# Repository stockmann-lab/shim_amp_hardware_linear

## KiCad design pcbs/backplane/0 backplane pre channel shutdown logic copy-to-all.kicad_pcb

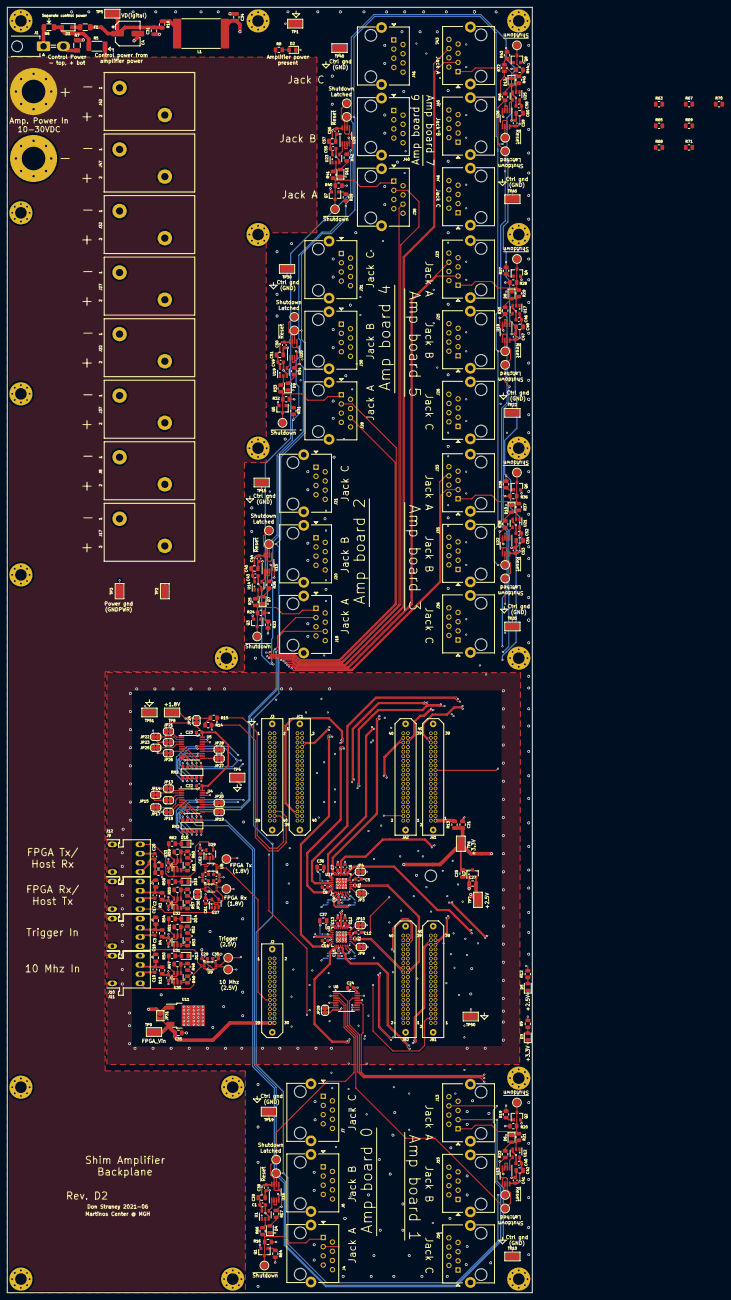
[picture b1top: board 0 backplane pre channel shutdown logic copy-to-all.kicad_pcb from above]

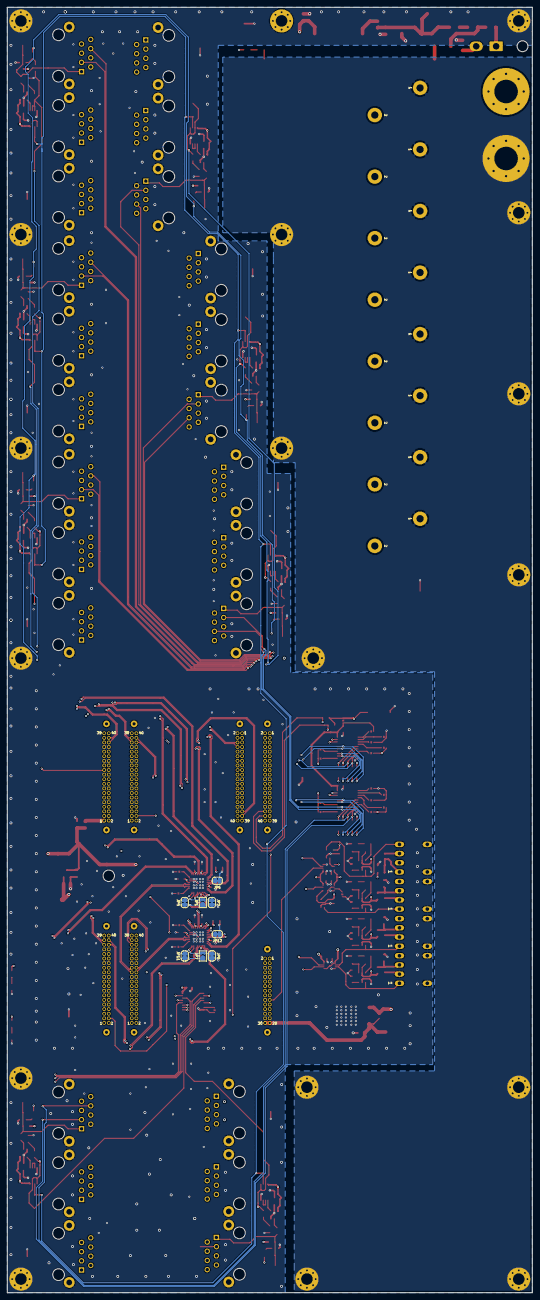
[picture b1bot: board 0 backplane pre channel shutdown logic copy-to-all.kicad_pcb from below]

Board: 6 copper layers, 145.0 x 355.0 mm, 340 parts (8 on the bottom side), 304 nets.

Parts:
C1, C2, C3, C5, C6, C7, C8, C9, C10, C11, C12, C13, C14, C15, C20, C22, C23, C24, C26, C28, C29, C30, C32, C33, C38, C40, C41, C43, C44, C46, C47, C49, C50, C52, C53, C55, C56, C58, C59, C61, C62, C63, C64, C65, C66: 100nF 50V X7R; C_0603_1608Metric
C4: 100uF 35V alum.; CP_Elec_6.3x9.9
C16, C17, C18, C19, C21, C25, C27, C31, C34, C35, C36, C37, C39, C42, C45, C48, C51, C54, C57, C60: 1uF 50V X7R; C_0805_2012Metric
D1: PMEG6010; D_SOD-123F
D2, D3, D5: Green; LED_0805_2012Metric
D4, D6, D7, D8, D9, D10, D11, D12: Red; LED_0805_2012Metric
D13, D14, D15, D16: Yellow; LED_0805_2012Metric
F1: TBD; Fuse_1206_3216Metric
H1, H2: 1/4", M6; MountingHole_6.5mm_Pad_Via
H3, H4, H5, H6, H7, H8, H9, H10, H11, H12, H13, H14, H15, H16, H17, H18, H19, H20: #4/M3; MountingHole_3.2mm_M3_Pad_Via
J1: Conn_01x02; Molex_Mini-Fit_Jr_5569-02A2_2x01_P4.20mm_Horizontal
J2: Conn_02x15_Odd_Even; Conn_Samtec_TFM-115-x1,3-x-D-WT
J3: Conn_02x20_Odd_Even; Conn_Samtec_TFM-120-x1,3-x-D-WT
J4, J6, J7, J13, J15, J16, J18, J20, J21, J23, J25, J26, J28, J30, J31, J33, J35, J36, J38, J40, J41, J43, J45, J46: RJ45_Shielded; RJ45_Amphenol_RJE06-188-1x20
J8, J17, J22, J27, J32, J37, J42, J47: Conn_01x02; Connector_Phoenix_1792229
J9, J10, J11: AFBR-2624Z; AFBR-xx2xZ
J12: AFBR-1624Z; AFBR-xx2xZ
JA1, JA2: Conn_02x20_Odd_Even; Conn_Samtec_TFM-120-x1,3-x-D-WT
JB1, JB2: Conn_02x20_Odd_Even; Conn_Samtec_TFM-120-x1,3-x-D-WT
JC1: Conn_02x20_Odd_Even; Conn_Samtec_TFM-120-x1,3-x-D-WT
JP1, JP7: Jumper_NC_Small; SolderJumper-2_P1.3mm_Open_TrianglePad1.0x1.5mm
JP2, JP3, JP4, JP5, JP6, JP8, JP9, JP10, JP11, JP12, JP13, JP14, JP15, JP17, JP18, JP19, JP20, JP21, JP22, JP23, JP24, JP25, JP26, JP27, JP28, JP29, JP30: Jumper_NC_Small; SolderJumper-2_P1.3mm_Bridged_RoundedPad1.0x1.5mm
JP31: Jumper_NO_Small; SolderJumper-2_P1.3mm_Open_TrianglePad1.0x1.5mm
L1: 500nH; L_Coilcraft_2929SQ-501
Q1, Q2, Q3, Q4, Q5, Q6, Q7, Q8: MMBT3904; SOT-23
R1, R2: 100; R_0402_1005Metric
R3, R4, R10, R11, R13, R18: 1; R_0805_2012Metric
R5: 10 0.25W; R_2010_5025Metric
R6, R7: 1; R_1206_3216Metric
R8: 15K; R_0805_2012Metric
R9, R16, R20, R21, R24, R25, R28, R29, R32, R33, R36, R37, R40, R41, R44, R45, R50, R54, R58, R62, R66: 1K; R_0805_2012Metric
R12: 560; R_0805_2012Metric
R14, R15: 4.7K; R_0805_2012Metric
R17, R22, R26, R30, R34, R38, R42, R46: 3.3K; R_0805_2012Metric
R19, R23, R27, R31, R35, R39, R43, R63, R64, R65, R67, R68, R69, R70, R71, R72: 20K; R_0805_2012Metric
R47, R51, R55, R59: 10K; R_0805_2012Metric
R48, R52, R56, R60: 6.81K; R_0805_2012Metric
R49, R53, R57, R61: 180K; R_0805_2012Metric
RN1, RN2: 4.7K; CTS_745C
TP1, TP2, TP3, TP4, TP5, TP6, TP7, TP8, TP9, TP10, TP15, TP19, TP22, TP30, TP35, TP40, TP45, TP50, TP51: TestPoint_Flag; TestPoint_Keystone_5019_Minature
TP11, TP14, TP16, TP20, TP21, TP23, TP26, TP29, TP31, TP34, TP36, TP39, TP41, TP44, TP46, TP49, TP52, TP53, TP54, TP55, TP56, TP57, TP58, TP59, TP60, TP61, TP62, TP63: TestPoint; TestPoint_Pad_D2.0mm
U1, U12, U14, U17, U19, U21, U23, U25, U27, U29: 74LVC1G14; SOT-23-5
U2, U3: CDCUN1208LP; VQFN-32-1EP_5x5mm_P0.5mm_EP3.45x3.45mm
U4, U5: PCA9544APW; TSSOP-20_4.4x6.5mm_P0.65mm
U6: 74HC151; TSSOP-16_4.4x5mm_P0.65mm
U7: AP2120N-2.5; SOT-23
U8, U9, U10: 74LVC2T45; VSSOP-8_2.3x2mm_P0.5mm
U11: 78M15; TO-252-2
U13, U15, U16, U18, U20, U22, U24, U26: 74LVC2G02; VSSOP-8_3.0x3.0mm_P0.65mm
U28: Snickerdoodle
U30, U31, U32, U33: LTC6993xS6-2; TSOT-23-6

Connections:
+1.8V: C26.2, C33.2, J3.3, JP24.1, R14.1, R15.1, TP8.1, U8.1, U8.5, U10.8
+2.5V: C1.1, C24.1, C27.2, C30.2, C38.1, C39.2, C40.1, C41.1, C42.2, C43.1, C44.1, C45.2, C46.1, C47.1, C48.2, C49.1, C50.1, C51.2, C52.1, C53.1, C54.2, C55.1, C56.1, C57.2, C58.1, C59.1, C60.2, JA1.3, JA2.3, JB1.3, JB2.3, JC1.3, R12.1, TP7.1, U1.5, U6.16, U7.2, U9.8, U12.5, U13.8, U14.5, U15.8, U16.8, U17.5, U18.8, U19.5, U20.8, U21.5, U22.8, U23.5, U24.8, U25.5, U26.8
+3V3: C5.1, C6.1, C7.1, C8.1, C9.1, C11.1, C12.1, C13.1, C14.1, C15.1, C21.2, C25.2, C28.2, C29.2, C32.2, C36.2, C37.2, C61.2, C62.2, C63.2, C64.2, C65.2, C66.2, JP1.1, JP5.1, JP7.1, JP11.1, JP17.2, JP18.2, JP19.2, JP20.2, JP25.2, JP26.2, JP27.2, JP28.2, R3.1, R4.1, R9.1, R10.1, R11.1, R13.2, R16.1, R20.1, R24.1, R28.1, R32.1, R36.1, R40.1, R44.1, R47.1, R51.1, R55.1, R59.1, RN1.5, RN1.10, RN2.5, RN2.10, TP6.1, U2.5, U2.11, U2.14, U2.22, U2.27, U3.5, U3.11, U3.14, U3.22, U3.27, U7.3, U8.8, U9.1, U9.5, U10.1, U10.5, U27.5, U29.5, U30.5, U31.5, U32.5, U33.5
+VDC: H1.1, J8.2, J17.2, J22.2, J27.2, J32.2, J37.2, J42.2, J47.2, R5.2, R8.1, TP2.1
/ADC_MISO+0: J6.8, JB2.11
/ADC_MISO+1: J15.8, JB1.14
/ADC_MISO+2: J20.8, JC1.14
/ADC_MISO+3: J35.8, JB1.26
/ADC_MISO+4: J30.8, JC1.32
/ADC_MISO+5: J25.8, JA1.14
/ADC_MISO+6: J40.8, JA2.29
/ADC_MISO+7: J45.8, JA1.35
/ADC_MISO-0: J6.7, JB2.13
/ADC_MISO-1: J15.7, JB1.12
/ADC_MISO-2: J20.7, JC1.12
/ADC_MISO-3: J35.7, JB1.24
/ADC_MISO-4: J30.7, JC1.30
/ADC_MISO-5: J25.7, JA1.12
/ADC_MISO-6: J40.7, JA2.31
/ADC_MISO-7: J45.7, JA1.37
/ADC_MOSI+0: J4.4, JB2.8
/ADC_MOSI+1: J13.4, JB1.17
/ADC_MOSI+2: J18.4, JC1.23
/ADC_MOSI+3: J33.4, JB2.29
/ADC_MOSI+4: J28.4, JC1.5
/ADC_MOSI+5: J23.4, JA1.17
/ADC_MOSI+6: J38.4, JA2.14
/ADC_MOSI+7: J43.4, JA2.32
/ADC_MOSI-0: J4.5, JB2.6
/ADC_MOSI-1: J13.5, JB1.19
/ADC_MOSI-2: J18.5, JC1.25
/ADC_MOSI-3: J33.5, JB2.31
/ADC_MOSI-4: J28.5, JC1.7
/ADC_MOSI-5: J23.5, JA1.19
/ADC_MOSI-6: J38.5, JA2.12
/ADC_MOSI-7: J43.5, JA2.30
/Activitiy Indicator (Rx)/In: J9.1, U27.2, U32.1
/Activity Indicator (Trigger)/In: J10.1, U9.2, U31.1
/Activity Indicator (Tx)/In: J12.4, U29.4, U33.1
/Amp board 0 interface/~Shutdown: J4.1, Q1.3, R16.2, R66.2, TP54.1
/Amp board 1 interface/~Shutdown: J13.1, Q2.3, R20.2, R21.2, TP55.1
/Amp board 2 interface/~Shutdown: J18.1, Q3.3, R24.2, R25.2, TP56.1
/Amp board 3 interface/~Shutdown: J33.1, Q6.3, R36.2, R37.2, TP59.1
/Amp board 4 interface/~Shutdown: J28.1, Q5.3, R32.2, R33.2, TP58.1
/Amp board 5 interface/~Shutdown: J23.1, Q4.3, R28.2, R29.2, TP57.1
/Amp board 6 interface/~Shutdown: J38.1, Q7.3, R40.2, R41.2, TP60.1
/Amp board 7 interface/~Shutdown: J43.1, Q8.3, R44.2, R45.2, TP61.1
/DAC_MISO+0: J6.2, JB2.14
/DAC_MISO+1: J15.2, JB1.11
/DAC_MISO+2: J20.2, JC1.17
/DAC_MISO+3: J35.2, JB1.29
/DAC_MISO+4: J30.2, JC1.38
/DAC_MISO+5: J25.2, JA1.11
/DAC_MISO+6: J40.2, JA2.20
/DAC_MISO+7: J45.2, JA1.26
/DAC_MISO-0: J6.1, JB2.12
/DAC_MISO-1: J15.1, JB1.13
/DAC_MISO-2: J20.1, JC1.19
/DAC_MISO-3: J35.1, JB1.31
/DAC_MISO-4: J30.1, JC1.36
/DAC_MISO-5: J25.1, JA1.13
/DAC_MISO-6: J40.1, JA2.18
/DAC_MISO-7: J45.1, JA1.24
/DAC_MOSI+0: J7.5, JB2.20
/DAC_MOSI+1: J16.5, JB1.5
/DAC_MOSI+2: J21.5, JC1.11
/DAC_MOSI+3: J36.5, JB1.23
/DAC_MOSI+4: J31.5, JA2.8
/DAC_MOSI+5: J26.5, JA1.5
/DAC_MOSI+6: J41.5, JA2.26
/DAC_MOSI+7: J46.5, JA1.32
/DAC_MOSI-0: J7.4, JB2.18
/DAC_MOSI-1: J16.4, JB1.7
/DAC_MOSI-2: J21.4, JC1.13
/DAC_MOSI-3: J36.4, JB1.25
/DAC_MOSI-4: J31.4, JA2.6
/DAC_MOSI-5: J26.4, JA1.7
/DAC_MOSI-6: J41.4, JA2.24
/DAC_MOSI-7: J46.4, JA1.30
/FPGA Board, Signal Distribution/10Mhz: J11.1, U9.3, U30.1
/FPGA Board, Signal Distribution/10Mhz_2.5: JB2.38, TP62.1, U9.6
/FPGA Board, Signal Distribution/FPGA_Vin: C35.2, J2.29, J2.30, JP31.2, TP9.1, U11.3
/FPGA Board, Signal Distribution/I2C_Pwr: C22.1, C23.1, JP21.1, JP24.2, U4.20, U5.20
/FPGA Board, Signal Distribution/LDAC+: JB2.26, R2.1, U3.4
/FPGA Board, Signal Distribution/LDAC-: JB2.24, R2.2, U3.3
/FPGA Board, Signal Distribution/SCL: J3.38, R15.2, U4.18, U5.18
/FPGA Board, Signal Distribution/SDA: J3.36, R14.2, U4.19, U5.19
/FPGA Board, Signal Distribution/Shutdown_Sense: JA2.4, U6.5
/FPGA Board, Signal Distribution/Shutdown_Sense_Sel0: JB2.4, U6.11
/FPGA Board, Signal Distribution/Shutdown_Sense_Sel1: JB1.4, U6.10
/FPGA Board, Signal Distribution/Shutdown_Sense_Sel2: JC1.4, U6.9
/FPGA Board, Signal Distribution/Trigger_2.5: JB2.36, TP53.1, U9.7
/FPGA Board, Signal Distribution/UART_Rx_FPGA: U10.2, U27.4
/FPGA Board, Signal Distribution/UART_Rx_FPGA_1.8: J3.37, TP63.1, U10.7
/FPGA Board, Signal Distribution/UART_Tx_FPGA: U8.6, U29.2
/FPGA Board, Signal Distribution/UART_Tx_FPGA_1.8: J3.35, TP52.1, U8.3
/FPGA Board, Signal Distribution/~FPGA_Rst_1.8: J2.19, U8.2
/FPGA Board, Signal Distribution/~SCKI+: JB2.23, R1.1, U2.4
/FPGA Board, Signal Distribution/~SCKI-: JB2.25, R1.2, U2.3
/SCKI+0: J7.2, U2.26
/SCKI+1: J16.2, U2.29
/SCKI+2: J21.2, U2.24
/SCKI+3: J36.2, U2.10
/SCKI+4: J31.2, U2.16
/SCKI+5: J26.2, U2.21
/SCKI+6: J41.2, U2.18
/SCKI+7: J46.2, U2.13
/SCKI-0: J7.1, U2.25
/SCKI-1: J16.1, U2.28
/SCKI-2: J21.1, U2.23
/SCKI-3: J36.1, U2.9
/SCKI-4: J31.1, U2.15
/SCKI-5: J26.1, U2.20
/SCKI-6: J41.1, U2.17
/SCKI-7: J46.1, U2.12
/SCKO+0: J6.5, JB2.35
/SCKO+1: J15.5, JB1.38
/SCKO+2: J20.5, JC1.8
/SCKO+3: J35.5, JB1.35
/SCKO+4: J30.5, JC1.35
/SCKO+5: J25.5, JA1.38
/SCKO+6: J40.5, JA2.38
/SCKO+7: J45.5, JA2.35
/SCKO-0: J6.4, JB2.37
/SCKO-1: J15.4, JB1.36
/SCKO-2: J20.4, JC1.6
/SCKO-3: J35.4, JB1.37
/SCKO-4: J30.4, JC1.37
/SCKO-5: J25.4, JA1.36
/SCKO-6: J40.4, JA2.36
/SCKO-7: J45.4, JA2.37
/SCL0: J4.3, RN1.2, U4.6
/SCL1: J13.3, RN1.4, U4.9
/SCL2: J18.3, RN1.8, U4.13
/SCL3: J33.3, RN1.6, U4.16
/SCL4: J28.3, RN2.2, U5.6
/SCL5: J23.3, RN2.4, U5.9
/SCL6: J38.3, RN2.8, U5.13
/SCL7: J43.3, RN2.6, U5.16
/SDA0: J4.6, RN1.1, U4.5
/SDA1: J13.6, RN1.3, U4.8
/SDA2: J18.6, RN1.9, U4.12
/SDA3: J33.6, RN1.7, U4.15
/SDA4: J28.6, RN2.1, U5.5
/SDA5: J23.6, RN2.3, U5.8
/SDA6: J38.6, RN2.9, U5.12
/SDA7: J43.6, RN2.7, U5.15
/Shutdown_Force: JA1.23, R19.2, R23.2, R27.2, R31.2, R35.2, R39.2, R43.2, R64.2
/Shutdown_Sense0: R17.2, R63.2, TP26.1, U6.4, U16.2, U16.3
/Shutdown_Sense1: R22.2, R65.2, TP14.1, U6.3, U13.2, U13.3
/Shutdown_Sense2: R26.2, R67.2, TP20.1, U6.2, U15.2, U15.3
/Shutdown_Sense3: R38.2, R70.2, TP39.1, U6.1, U22.2, U22.3
/Shutdown_Sense4: R34.2, R69.2, TP34.1, U6.15, U20.2, U20.3
/Shutdown_Sense5: R30.2, R68.2, TP29.1, U6.14, U18.2, U18.3
/Shutdown_Sense6: R42.2, R71.2, TP44.1, U6.13, U24.2, U24.3
/Shutdown_Sense7: R46.2, R72.2, TP49.1, U6.12, U26.2, U26.3
/~ADC_CS+0: J4.7, JB2.17
/~ADC_CS+1: J13.7, JB1.8
/~ADC_CS+2: J18.7, JC1.29
/~ADC_CS+3: J33.7, JB2.32
/~ADC_CS+4: J28.7, JC1.26
/~ADC_CS+5: J23.7, JA1.8
/~ADC_CS+6: J38.7, JA2.5
/~ADC_CS+7: J43.7, JA2.17
/~ADC_CS-0: J4.8, JB2.19
/~ADC_CS-1: J13.8, JB1.6
/~ADC_CS-2: J18.8, JC1.31
/~ADC_CS-3: J33.8, JB2.30
/~ADC_CS-4: J28.8, JC1.24
/~ADC_CS-5: J23.8, JA1.6
/~ADC_CS-6: J38.8, JA2.7
/~ADC_CS-7: J43.8, JA2.19
/~DAC_CS+0: J7.6, JB2.5
/~DAC_CS+1: J16.6, JB1.20
/~DAC_CS+2: J21.6, JC1.20
/~DAC_CS+3: J36.6, JB1.32
/~DAC_CS+4: J31.6, JA2.11
/~DAC_CS+5: J26.6, JA1.20
/~DAC_CS+6: J41.6, JA2.23
/~DAC_CS+7: J46.6, JA1.29
/~DAC_CS-0: J7.3, JB2.7
/~DAC_CS-1: J16.3, JB1.18
/~DAC_CS-2: J21.3, JC1.18
/~DAC_CS-3: J36.3, JB1.30
/~DAC_CS-4: J31.3, JA2.13
/~DAC_CS-5: J26.3, JA1.18
/~DAC_CS-6: J41.3, JA2.25
/~DAC_CS-7: J46.3, JA1.31
/~LDAC+0: J7.8, U3.25
/~LDAC+1: J16.8, U3.28
/~LDAC+2: J21.8, U3.23
/~LDAC+3: J36.8, U3.9
/~LDAC+4: J31.8, U3.12
/~LDAC+5: J26.8, U3.17
/~LDAC+6: J41.8, U3.15
/~LDAC+7: J46.8, U3.20
/~LDAC-0: J7.7, U3.26
/~LDAC-1: J16.7, U3.29
/~LDAC-2: J21.7, U3.24
/~LDAC-3: J36.7, U3.10
/~LDAC-4: J31.7, U3.13
/~LDAC-5: J26.7, U3.18
/~LDAC-6: J41.7, U3.16
/~LDAC-7: J46.7, U3.21
/~Shutdown_Reset: TP11.1, TP16.1, TP21.1, TP23.1, TP31.1, TP36.1, TP41.1, TP46.1, U13.6, U15.6, U16.6, U18.6, U20.6, U22.6, U24.6, U26.6
GND: C1.2, C2.2, C3.2, C4.2, C5.2, C6.2, C7.2, C8.2, C9.2, C10.2, C11.2, C12.2, C13.2, C14.2, C15.2, C16.1, C17.1, C18.1, C19.1, C20.2, C21.1, C22.2, C23.2, C24.2, C25.1, C26.1, C27.1, C28.1, C29.1, C30.1, C31.1, C32.1, C33.1, C34.1, C35.1, C36.1, C37.1, C38.2, C39.1, C40.2, C41.2, C42.1, C43.2, C44.2, C45.1, C46.2, C47.2, C48.1, C49.2, C50.2, C51.1, C52.2, C53.2, C54.1, C55.2, C56.2, C57.1, C58.2, C59.2, C60.1, C61.1, C62.1, C63.1, C64.1, C65.1, C66.1, D3.1, D4.1, D5.1, D6.1, D7.1, D8.1, D9.1, D10.1, D11.1, D12.1, D13.1, D14.1, D15.1, D16.1, H3.1, H4.1, H6.1, H8.1, H10.1, H12.1, H13.1, H15.1, J2.5, J2.6, J2.9, J2.10, J2.20, J2.26, J2.27, J2.28, J3.9, J3.10, J3.15, J3.16, J3.21, J3.22, J3.27, J3.28, J3.33, J3.34, J4.2, J4.SH, J6.SH, J7.SH, J9.2, J9.5, J9.8, J10.2, J10.5, J10.8, J11.2, J11.5, J11.8, J12.3, J12.5, J12.8, J13.2, J13.SH, J15.SH, J16.SH, J18.2, J18.SH, J20.SH, J21.SH, J23.2, J23.SH, J25.SH, J26.SH, J28.2, J28.SH, J30.SH, J31.SH, J33.2, J33.SH, J35.SH, J36.SH, J38.2, J38.SH, J40.SH, J41.SH, J43.2, J43.SH, J45.SH, J46.SH, JA1.9, JA1.10, JA1.15, JA1.16, JA1.21, JA1.22, JA1.27, JA1.28, JA1.33, JA1.34, JA2.9, JA2.10, JA2.15, JA2.16, JA2.21, JA2.22, JA2.27, JA2.28, JA2.33, JA2.34, JB1.9, JB1.10, JB1.15, JB1.16, JB1.21, JB1.22, JB1.27, JB1.28, JB1.33, JB1.34, JB2.9, JB2.10, JB2.15, JB2.16, JB2.21, JB2.22, JB2.27, JB2.28, JB2.33, JB2.34, JC1.9, JC1.10, JC1.15, JC1.16, JC1.21, JC1.22, JC1.27, JC1.28, JC1.33, JC1.34, JP2.2, JP3.1, JP4.1, JP6.1, JP8.2, JP9.1, JP10.1, JP12.1, JP13.1, JP14.1, JP15.1, JP22.1, JP23.1, JP29.1, JP30.1, Q1.2, Q2.2, Q3.2, Q4.2, Q5.2, Q6.2, Q7.2, Q8.2, R7.1, R48.2, R49.2, R52.2, R53.2, R56.2, R57.2, R60.2, R61.2, TP1.1, TP4.1, TP10.1, TP15.1, TP19.1, TP22.1, TP30.1, TP35.1, TP40.1, TP45.1, TP50.1, TP51.1, U1.3, U2.6, U2.7, U2.33, U3.6, U3.7, U3.33, U4.10, U5.10, U6.8, U7.1, U8.4, U9.4, U10.4, U11.2, U12.3, U13.4, U14.3, U15.4, U16.4, U17.3, U18.4, U19.3, U20.4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
GNDPWR: D2.1, H2.1, H5.1, H7.1, H9.1, H11.1, H14.1, H16.1, H17.1, H18.1, H19.1, H20.1, J8.1, J17.1, J22.1, J27.1, J32.1, J37.1, J42.1, J47.1, TP3.1
unnamed: C10.1, C18.2, J11.3, R10.2
unnamed: C2.1, C16.2, J9.3, R3.2
unnamed: C3.1, C17.2, J10.3, R4.2
unnamed: C19.2, C20.1, J12.1, R11.2
unnamed: C34.2, JP31.1, L1.2, U11.1
unnamed: D1.1, F1.2
unnamed: D1.2, R5.1, R6.1
unnamed: D2.2, R8.2
unnamed: D3.2, R9.2
unnamed: D4.2, R17.1
unnamed: D5.2, R12.2
unnamed: D6.2, R22.1
unnamed: D7.2, R26.1
unnamed: D8.2, R30.1
unnamed: D9.2, R34.1
unnamed: D10.2, R38.1
unnamed: D11.2, R42.1
unnamed: D12.2, R46.1
unnamed: D13.2, R50.2
unnamed: D14.2, R54.2
unnamed: D15.2, R58.2
unnamed: D16.2, R62.2
unnamed: J1.1, R6.2
unnamed: J1.2, R7.2
unnamed: JA1.1, R13.1
unnamed: JP1.2, JP2.1, U2.31
unnamed: JP3.2, U2.2
unnamed: JP4.2, U2.8
unnamed: JP5.2, U2.32
unnamed: JP6.2, U2.19
unnamed: JP7.2, JP8.1, U3.31
unnamed: JP9.2, U3.2
unnamed: JP10.2, U3.8
unnamed: JP11.2, U3.32
unnamed: JP12.2, U3.19
unnamed: JP13.2, U4.1
unnamed: JP14.2, U4.2
unnamed: JP15.2, U4.3
unnamed: JP17.1, U4.4
unnamed: JP18.1, U4.7
unnamed: JP19.1, U4.11
unnamed: JP20.1, U4.14
unnamed: JP21.2, U5.1
unnamed: JP22.2, U5.2
unnamed: JP23.2, U5.3
unnamed: JP25.1, U5.4
unnamed: JP26.1, U5.7
unnamed: JP27.1, U5.11
unnamed: JP28.1, U5.14
unnamed: JP29.2, U6.7
unnamed: JP30.2, U10.3
unnamed: L1.1, R18.1
unnamed: Q1.1, R63.1, R64.1
unnamed: Q2.1, R19.1, R65.1
unnamed: Q3.1, R23.1, R67.1
unnamed: Q4.1, R27.1, R68.1
unnamed: Q5.1, R31.1, R69.1
unnamed: Q6.1, R35.1, R70.1
unnamed: Q7.1, R39.1, R71.1
unnamed: Q8.1, R43.1, R72.1
unnamed: R21.1, U12.2
unnamed: R25.1, U14.2
unnamed: R29.1, U17.2
unnamed: R33.1, U19.2
unnamed: R37.1, U21.2
unnamed: R41.1, U23.2
unnamed: R45.1, U25.2
unnamed: R47.2, R48.1, U30.4
unnamed: R49.1, U30.3
unnamed: R50.1, U30.6
unnamed: R51.2, R52.1, U31.4
unnamed: R53.1, U31.3
unnamed: R54.1, U31.6
unnamed: R55.2, R56.1, U32.4
unnamed: R57.1, U32.3
unnamed: R58.1, U32.6
unnamed: R59.2, R60.1, U33.4
unnamed: R61.1, U33.3
unnamed: R62.1, U33.6
unnamed: R66.1, U1.2
unnamed: U1.4, U16.1
unnamed: U12.4, U13.1
unnamed: U13.5, U13.7
unnamed: U14.4, U15.1
unnamed: U15.5, U15.7
unnamed: U16.5, U16.7
unnamed: U17.4, U18.1
unnamed: U18.5, U18.7
unnamed: U19.4, U20.1
unnamed: U20.5, U20.7
unnamed: U21.4, U22.1
unnamed: U22.5, U22.7
unnamed: U23.4, U24.1
unnamed: U24.5, U24.7
unnamed: U25.4, U26.1
unnamed: U26.5, U26.7
VD: C4.1, C31.2, F1.1, R18.2, TP5.1

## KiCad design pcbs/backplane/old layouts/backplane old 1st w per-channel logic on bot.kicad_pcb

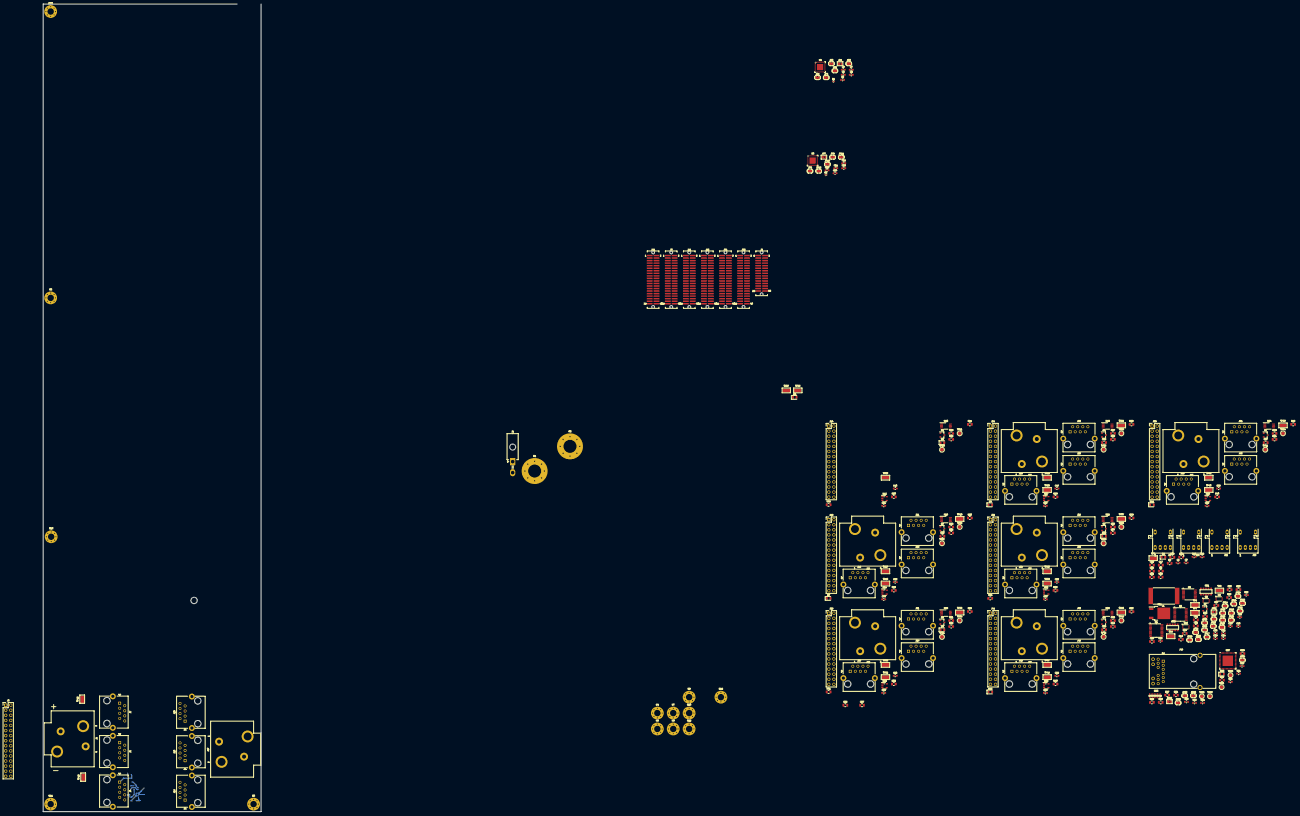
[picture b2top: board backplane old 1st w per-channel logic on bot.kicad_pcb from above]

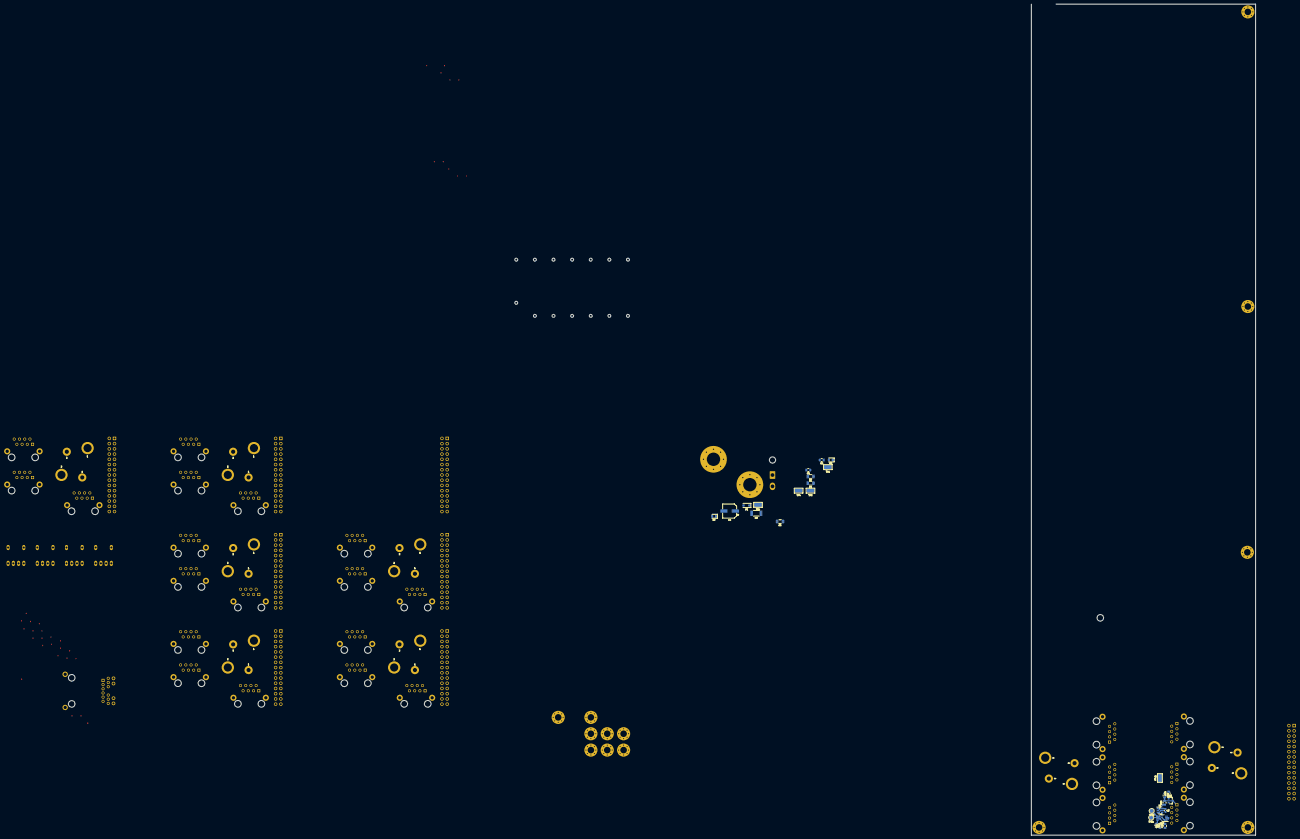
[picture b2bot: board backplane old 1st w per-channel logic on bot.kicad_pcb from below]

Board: 2 copper layers, 109.0 x 404.0 mm, 331 parts (27 on the bottom side), 338 nets.

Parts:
C1, C2, C3, C5, C6, C7, C8, C9, C10, C11, C12, C13, C14, C15, C20, C22, C23, C24, C26, C28, C29, C30, C32, C33, C38, C40, C41, C43, C44, C46, C47, C49, C50, C52, C53, C55, C56, C58, C59, C62, C63, C64, C65: 100nF 50V X7R; C_0603_1608Metric
C4: 100uF 35V alum.; CP_Elec_6.3x9.9
C16, C17, C18, C19, C21, C25, C27, C31, C34, C35, C36, C37, C39, C42, C45, C48, C51, C54, C57, C60: 1uF 50V X7R; C_0805_2012Metric
C61: 10nF 50V X7R; C_0603_1608Metric
C66: 100pF 50V NP0; C_0603_1608Metric
D1: PMEG6010; D_SOD-123F
D2, D3, D5: Green; LED_0805_2012Metric
D4, D6, D7, D8, D9, D10, D11, D12, D13: Red; LED_0805_2012Metric
F1: TBD; Fuse_1206_3216Metric
H1, H2: 1/4", M6; MountingHole_6.5mm_Pad_Via
H3, H4, H5, H6, H7, H8, H9, H10, H11, H12, H13, H14, H15: #4/M3; MountingHole_3.2mm_M3_Pad_Via
J1: Conn_01x02; Molex_Mini-Fit_Jr_5569-02A2_2x01_P4.20mm_Horizontal
J2: Conn_02x15_Odd_Even; Conn_Samtec_TFM-115-x2-L-D-A
J3: Conn_02x20_Odd_Even; Conn_Samtec_TFM-120-x2-L-D-A
J4, J6, J7, J13, J15, J16, J18, J20, J21, J23, J25, J26, J28, J30, J31, J33, J35, J36, J38, J40, J41, J43, J45, J46: RJ45_Shielded; RJ45_Amphenol_RJE06-188-1x20
J5, J14, J19, J24, J29, J34, J39, J44: Conn_02x15; PinHeader_2x15_P2.54mm_Vertical
J8, J17, J22, J27, J32, J37, J42, J47: Conn_01x02; Connector_Combo_Molex_386608802_Phoenix_1792229
J9, J10, J11: AFBR-2624Z; AFBR-xx2xZ
J12: AFBR-1624Z; AFBR-xx2xZ
J48: JK0654219; RJ45_Pulse_JK0654219NL_Horizontal
JA1, JA2: Conn_02x20_Odd_Even; Conn_Samtec_TFM-120-x2-L-D-A
JB1, JB2: Conn_02x20_Odd_Even; Conn_Samtec_TFM-120-x2-L-D-A
JC1: Conn_02x20_Odd_Even; Conn_Samtec_TFM-120-x2-L-D-A
JP1, JP7: Jumper_NC_Small; SolderJumper-2_P1.3mm_Open_TrianglePad1.0x1.5mm
JP2, JP3, JP4, JP5, JP6, JP8, JP9, JP10, JP11, JP12, JP13, JP14, JP15, JP16, JP17, JP18, JP19, JP20, JP21, JP22, JP23, JP24, JP25, JP26, JP27, JP28, JP29, JP30, JP32, JP34, JP35, JP36: Jumper_NC_Small; SolderJumper-2_P1.3mm_Bridged_RoundedPad1.0x1.5mm
JP31, JP33: Jumper_NO_Small; SolderJumper-2_P1.3mm_Open_TrianglePad1.0x1.5mm
L1: 500nH; L_Coilcraft_2929SQ-501
Q1, Q2, Q3, Q4, Q5, Q6, Q7, Q8: MMBT3904; SOT-23
R1, R2: 100; R_0402_1005Metric
R3, R4, R10, R11, R13, R18: 1; R_0805_2012Metric
R5: 10 0.25W; R_2010_5025Metric
R6, R7: 1; R_1206_3216Metric
R8: 15K; R_0805_2012Metric
R9, R16, R20, R21, R24, R25, R28, R29, R32, R33, R36, R37, R40, R41, R44, R45, R47, R49, R52, R66: 1K; R_0805_2012Metric
R12: 560; R_0805_2012Metric
R14, R15: 4.7K; R_0805_2012Metric
R17, R22, R26, R30, R34, R38, R42, R46: 3.3K; R_0805_2012Metric
R19, R23, R27, R31, R35, R39, R43, R64: 20K; R_0805_2012Metric
R48: 2K; R_0805_2012Metric
R50: 100; R_0805_2012Metric
R51: 10K; R_0805_2012Metric
RN1, RN2: 4.7K; CTS_745C
RN3: 33; CTS_742x163
TP1, TP2, TP3, TP4, TP5, TP6, TP7, TP8, TP9, TP10, TP12, TP13, TP15, TP17, TP18, TP19, TP22, TP24, TP25, TP27, TP28, TP30, TP32, TP33, TP35, TP37, TP38, TP40, TP42, TP43, TP45, TP47, TP48: TestPoint_Flag; TestPoint_Keystone_5019_Minature
TP11, TP14, TP16, TP20, TP21, TP23, TP26, TP29, TP31, TP34, TP36, TP39, TP41, TP44, TP46, TP49, TP50, TP51, TP52, TP53: TestPoint; TestPoint_Pad_D2.0mm
U1, U12, U14, U17, U19, U21, U23, U25: 74LVC1G17; SOT-23-5
U2, U3: CDCUN1208LP; VQFN-32-1EP_5x5mm_P0.5mm_EP3.45x3.45mm
U4, U5: PCA9544APW; TSSOP-20_4.4x6.5mm_P0.65mm
U6: 74HC151; TSSOP-16_4.4x5mm_P0.65mm
U7: AP2120N-2.5; SOT-23
U8, U9, U10: 74LVC2T45; VSSOP-8_2.3x2mm_P0.5mm
U11: 78M15; TO-252-2
U13, U15, U16, U18, U20, U22, U24, U26: 74LVC2G00; VSSOP-8_3.0x3.0mm_P0.65mm
U27: VSC8541XMV-0x; QFN-68-1EP_8x8mm_P0.4mm_EP5.2x5.2mm
U28: Snickerdoodle

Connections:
+1.8V: C26.2, C33.2, J3.3, JP16.1, JP24.1, R14.1, R15.1, R51.1, TP8.1, U8.1, U8.5, U10.8, U27.22, U27.28, U27.39, U27.44, U27.49
+2.5V: C1.1, C24.1, C27.2, C30.2, C38.1, C39.2, C40.1, C41.1, C42.2, C43.1, C44.1, C45.2, C46.1, C47.1, C48.2, C49.1, C50.1, C51.2, C52.1, C53.1, C54.2, C55.1, C56.1, C57.2, C58.1, C59.1, C60.2, JA1.3, JA2.3, JB1.3, JB2.3, JC1.3, JP21.1, R12.1, TP7.1, U1.5, U6.16, U7.2, U9.8, U12.5, U13.8, U14.5, U15.8, U16.8, U17.5, U18.8, U19.5, U20.8, U21.5, U22.8, U23.5, U24.8, U25.5, U26.8
+3V3: C5.1, C6.1, C7.1, C8.1, C9.1, C11.1, C12.1, C13.1, C14.1, C15.1, C21.2, C25.2, C28.2, C29.2, C32.2, C36.2, C37.2, J48.14, J48.16, JP1.1, JP5.1, JP7.1, JP11.1, JP17.2, JP18.2, JP19.2, JP20.2, JP25.2, JP26.2, JP27.2, JP28.2, JP36.1, R3.1, R4.1, R9.1, R10.1, R11.1, R13.2, R16.1, R20.1, R24.1, R28.1, R32.1, R36.1, R40.1, R44.1, R52.1, RN1.5, RN1.10, RN2.5, RN2.10, TP6.1, U2.5, U2.11, U2.14, U2.22, U2.27, U3.5, U3.11, U3.14, U3.22, U3.27, U7.3, U8.8, U9.1, U9.5, U10.1, U10.5, U27.58
+VDC: H1.1, J8.2, J17.2, J22.2, J27.2, J32.2, J37.2, J42.2, J47.2, R5.2, R8.1, TP12.1, TP17.1, TP24.1, TP25.1, TP32.1, TP37.1, TP42.1, TP47.1
/ADC_MISO+0: J5.17, J6.8, JB2.11
/ADC_MISO+1: J14.17, J15.8, JB1.14
/ADC_MISO+2: J19.17, J20.8, JC1.14
/ADC_MISO+3: J34.17, J35.8, JB1.32
/ADC_MISO+4: J29.17, J30.8, JC1.32
/ADC_MISO+5: J24.17, J25.8, JA1.14
/ADC_MISO+6: J39.17, J40.8, JA2.17
/ADC_MISO+7: J44.17, J45.8, JA2.29
/ADC_MISO-0: J5.18, J6.7, JB2.13
/ADC_MISO-1: J14.18, J15.7, JB1.12
/ADC_MISO-2: J19.18, J20.7, JC1.12
/ADC_MISO-3: J34.18, J35.7, JB1.30
/ADC_MISO-4: J29.18, J30.7, JC1.30
/ADC_MISO-5: J24.18, J25.7, JA1.12
/ADC_MISO-6: J39.18, J40.7, JA2.19
/ADC_MISO-7: J44.18, J45.7, JA2.31
/ADC_MOSI+0: J4.4, J5.20, JB2.8
/ADC_MOSI+1: J13.4, J14.20, JB1.17
/ADC_MOSI+2: J18.4, J19.20, JC1.11
/ADC_MOSI+3: J33.4, J34.20, JB2.32
/ADC_MOSI+4: J28.4, J29.20, JC1.29
/ADC_MOSI+5: J23.4, J24.20, JA1.17
/ADC_MOSI+6: J38.4, J39.20, JA2.14
/ADC_MOSI+7: J43.4, J44.20, JA1.32
/ADC_MOSI-0: J4.5, J5.21, JB2.6
/ADC_MOSI-1: J13.5, J14.21, JB1.19
/ADC_MOSI-2: J18.5, J19.21, JC1.13
/ADC_MOSI-3: J33.5, J34.21, JB2.30
/ADC_MOSI-4: J28.5, J29.21, JC1.31
/ADC_MOSI-5: J23.5, J24.21, JA1.19
/ADC_MOSI-6: J38.5, J39.21, JA2.12
/ADC_MOSI-7: J43.5, J44.21, JA1.30
/Amp board 0 interface/~Shutdown: J4.1, J5.29, Q1.3, R16.2, R66.2
/Amp board 1 interface/~Shutdown: J13.1, J14.29, Q2.3, R20.2, R21.2
/Amp board 2 interface/~Shutdown: J18.1, J19.29, Q3.3, R24.2, R25.2
/Amp board 3 interface/~Shutdown: J33.1, J34.29, Q6.3, R36.2, R37.2
/Amp board 4 interface/~Shutdown: J28.1, J29.29, Q5.3, R32.2, R33.2
/Amp board 5 interface/~Shutdown: J23.1, J24.29, Q4.3, R28.2, R29.2
/Amp board 6 interface/~Shutdown: J38.1, J39.29, Q7.3, R40.2, R41.2
/Amp board 7 interface/~Shutdown: J43.1, J44.29, Q8.3, R44.2, R45.2
/DAC_MISO+0: J5.13, J6.2, JB2.14
/DAC_MISO+1: J14.13, J15.2, JB1.11
/DAC_MISO+2: J19.13, J20.2, JC1.17
/DAC_MISO+3: J34.13, J35.2, JB1.29
/DAC_MISO+4: J29.13, J30.2, JC1.38
/DAC_MISO+5: J24.13, J25.2, JA1.11
/DAC_MISO+6: J39.13, J40.2, JA2.20
/DAC_MISO+7: J44.13, J45.2, JA2.32
/DAC_MISO-0: J5.12, J6.1, JB2.12
/DAC_MISO-1: J14.12, J15.1, JB1.13
/DAC_MISO-2: J19.12, J20.1, JC1.19
/DAC_MISO-3: J34.12, J35.1, JB1.31
/DAC_MISO-4: J29.12, J30.1, JC1.36
/DAC_MISO-5: J24.12, J25.1, JA1.13
/DAC_MISO-6: J39.12, J40.1, JA2.18
/DAC_MISO-7: J44.12, J45.1, JA2.30
/DAC_MOSI+0: J5.9, J7.5, JB2.20
/DAC_MOSI+1: J14.9, J16.5, JB1.5
/DAC_MOSI+2: J19.9, J21.5, JC1.23
/DAC_MOSI+3: J34.9, J36.5, JB1.23
/DAC_MOSI+4: J29.9, J31.5, JA2.8
/DAC_MOSI+5: J24.9, J26.5, JA1.5
/DAC_MOSI+6: J39.9, J41.5, JA2.26
/DAC_MOSI+7: J44.9, J46.5, JA1.26
/DAC_MOSI-0: J5.10, J7.4, JB2.18
/DAC_MOSI-1: J14.10, J16.4, JB1.7
/DAC_MOSI-2: J19.10, J21.4, JC1.25
/DAC_MOSI-3: J34.10, J36.4, JB1.25
/DAC_MOSI-4: J29.10, J31.4, JA2.6
/DAC_MOSI-5: J24.10, J26.4, JA1.7
/DAC_MOSI-6: J39.10, J41.4, JA2.24
/DAC_MOSI-7: J44.10, J46.4, JA1.24
/Ethernet interface/Eth_Clk: JA1.25, R50.1, U27.63
/Ethernet interface/Fastlink_Fail_LED: D13.1, U27.52
/Ethernet interface/LED0: R47.2, U27.60
/Ethernet interface/LED1: R49.2, U27.59
/Ethernet interface/RGMII_GTX_CLK: J3.5, U27.37
/Ethernet interface/RGMII_RXD0: J3.12, RN3.12
/Ethernet interface/RGMII_RXD1: J3.17, RN3.11
/Ethernet interface/RGMII_RXD2: J3.19, RN3.10
/Ethernet interface/RGMII_RXD3: J3.20, RN3.9
/Ethernet interface/RGMII_RX_CLK: J3.14, RN3.14
/Ethernet interface/RGMII_RX_CTL: J3.18, RN3.13
/Ethernet interface/RGMII_TXD0: J3.7, U27.38
/Ethernet interface/RGMII_TXD1: J3.8, U27.40
/Ethernet interface/RGMII_TXD2: J3.6, U27.41
/Ethernet interface/RGMII_TXD3: J3.11, U27.42
/Ethernet interface/RGMII_TX_CTL: J3.13, U27.33
/FPGA Board, Signal Distribution/10Mhz: J11.1, U9.3
/FPGA Board, Signal Distribution/10Mhz_2.5: JB2.38, U9.6
/FPGA Board, Signal Distribution/FPGA_Vin: C35.2, J2.29, J2.30, JP31.2, TP9.1, U11.3
/FPGA Board, Signal Distribution/SCKI+: JB2.26, R1.2, U2.3
/FPGA Board, Signal Distribution/SCKI-: JB2.24, R1.1, U2.4
/FPGA Board, Signal Distribution/SCL: J3.38, R15.2, U4.18, U5.18
/FPGA Board, Signal Distribution/SDA: J3.36, R14.2, U4.19, U5.19
/FPGA Board, Signal Distribution/Shutdown_Sense: JA2.4, U6.5
/FPGA Board, Signal Distribution/Shutdown_Sense_Sel0: JB2.4, U6.11
/FPGA Board, Signal Distribution/Shutdown_Sense_Sel1: JB1.4, U6.10
/FPGA Board, Signal Distribution/Shutdown_Sense_Sel2: JC1.4, U6.9
/FPGA Board, Signal Distribution/Trigger: J10.1, U9.2
/FPGA Board, Signal Distribution/Trigger_2.5: JB2.36, U9.7
/FPGA Board, Signal Distribution/UART_Rx_FPGA: J9.1, U10.2
/FPGA Board, Signal Distribution/UART_Rx_FPGA_1.8: J3.37, U10.7
/FPGA Board, Signal Distribution/UART_Tx_FPGA: J12.4, U8.6
/FPGA Board, Signal Distribution/UART_Tx_FPGA_1.8: J3.35, U8.3
/FPGA Board, Signal Distribution/~FPGA_Rst_1.8: J2.19, U8.2
/FPGA Board, Signal Distribution/~LDAC+: JB2.23, R2.2, U3.3
/FPGA Board, Signal Distribution/~LDAC-: JB2.25, R2.1, U3.4
/SCKI+0: J5.7, J7.2, U2.10
/SCKI+1: J14.7, J16.2, U2.13
/SCKI+2: J19.7, J21.2, U2.16
/SCKI+3: J34.7, J36.2, U2.18
/SCKI+4: J29.7, J31.2, U2.21
/SCKI+5: J24.7, J26.2, U2.24
/SCKI+6: J39.7, J41.2, U2.26
/SCKI+7: J44.7, J46.2, U2.29
/SCKI-0: J5.8, J7.1, U2.9
/SCKI-1: J14.8, J16.1, U2.12
/SCKI-2: J19.8, J21.1, U2.15
/SCKI-3: J34.8, J36.1, U2.17
/SCKI-4: J29.8, J31.1, U2.20
/SCKI-5: J24.8, J26.1, U2.23
/SCKI-6: J39.8, J41.1, U2.25
/SCKI-7: J44.8, J46.1, U2.28
/SCKO+0: J5.15, J6.5, JB2.35
/SCKO+1: J14.15, J15.5, JB1.38
/SCKO+2: J19.15, J20.5, JC1.8
/SCKO+3: J34.15, J35.5, JB1.35
/SCKO+4: J29.15, J30.5, JC1.35
/SCKO+5: J24.15, J25.5, JA1.38
/SCKO+6: J39.15, J40.5, JA2.38
/SCKO+7: J44.15, J45.5, JA2.35
/SCKO-0: J5.14, J6.4, JB2.37
/SCKO-1: J14.14, J15.4, JB1.36
/SCKO-2: J19.14, J20.4, JC1.6
/SCKO-3: J34.14, J35.4, JB1.37
/SCKO-4: J29.14, J30.4, JC1.37
/SCKO-5: J24.14, J25.4, JA1.36
/SCKO-6: J39.14, J40.4, JA2.36
/SCKO-7: J44.14, J45.4, JA2.37
/SCL0: J4.3, J5.28, RN1.2, U4.6
/SCL1: J13.3, J14.28, RN1.4, U4.9
/SCL2: J18.3, J19.28, RN1.7, U4.13
/SCL3: J33.3, J34.28, RN1.9, U4.16
/SCL4: J28.3, J29.28, RN2.2, U5.6
/SCL5: J23.3, J24.28, RN2.4, U5.9
/SCL6: J38.3, J39.28, RN2.7, U5.13
/SCL7: J43.3, J44.28, RN2.9, U5.16
/SDA0: J4.6, J5.27, RN1.1, U4.5
/SDA1: J13.6, J14.27, RN1.3, U4.8
/SDA2: J18.6, J19.27, RN1.6, U4.12
/SDA3: J33.6, J34.27, RN1.8, U4.15
/SDA4: J28.6, J29.27, RN2.1, U5.5
/SDA5: J23.6, J24.27, RN2.3, U5.8
/SDA6: J38.6, J39.27, RN2.6, U5.12
/SDA7: J43.6, J44.27, RN2.8, U5.15
/Shutdown_Force: JA1.23, R19.2, R23.2, R27.2, R31.2, R35.2, R39.2, R43.2, R64.2
/Shutdown_Sense0: R17.2, TP26.1, U6.4, U16.5, U16.7
/Shutdown_Sense1: R22.2, TP14.1, U6.3, U13.5, U13.7
/Shutdown_Sense2: R26.2, TP20.1, U6.2, U15.5, U15.7
/Shutdown_Sense3: R38.2, TP39.1, U6.1, U22.5, U22.7
/Shutdown_Sense4: R34.2, TP34.1, U6.15, U20.5, U20.7
/Shutdown_Sense5: R30.2, TP29.1, U6.14, U18.5, U18.7
/Shutdown_Sense6: R42.2, TP44.1, U6.13, U24.5, U24.7
/Shutdown_Sense7: R46.2, TP49.1, U6.12, U26.5, U26.7
/~ADC_CS+0: J4.7, J5.23, JB2.5
/~ADC_CS+1: J13.7, J14.23, JB1.20
/~ADC_CS+2: J18.7, J19.23, JC1.5
/~ADC_CS+3: J33.7, J34.23, JB2.29
/~ADC_CS+4: J28.7, J29.23, JC1.26
/~ADC_CS+5: J23.7, J24.23, JA1.20
/~ADC_CS+6: J38.7, J39.23, JA2.11
/~ADC_CS+7: J43.7, J44.23, JA1.35
/~ADC_CS-0: J4.8, J5.22, JB2.7
/~ADC_CS-1: J13.8, J14.22, JB1.18
/~ADC_CS-2: J18.8, J19.22, JC1.7
/~ADC_CS-3: J33.8, J34.22, JB2.31
/~ADC_CS-4: J28.8, J29.22, JC1.24
/~ADC_CS-5: J23.8, J24.22, JA1.18
/~ADC_CS-6: J38.8, J39.22, JA2.13
/~ADC_CS-7: J43.8, J44.22, JA1.37
/~DAC_CS+0: J5.4, J7.6
/~DAC_CS+1: J14.4, J16.6
/~DAC_CS+2: J19.4, J21.6
/~DAC_CS+3: J34.4, J36.6
/~DAC_CS+4: J29.4, J31.6
/~DAC_CS+5: J24.4, J26.6
/~DAC_CS+6: J39.4, J41.6
/~DAC_CS+7: J44.4, J46.6
/~DAC_CS-0: J5.5, J7.3
/~DAC_CS-1: J14.5, J16.3
/~DAC_CS-2: J19.5, J21.3
/~DAC_CS-3: J34.5, J36.3
/~DAC_CS-4: J29.5, J31.3
/~DAC_CS-5: J24.5, J26.3
/~DAC_CS-6: J39.5, J41.3
/~DAC_CS-7: J44.5, J46.3
/~LDAC+0: J5.3, J7.8
/~LDAC+1: J14.3, J16.8
/~LDAC+2: J19.3, J21.8
/~LDAC+3: J34.3, J36.8
/~LDAC+4: J29.3, J31.8
/~LDAC+5: J24.3, J26.8
/~LDAC+6: J39.3, J41.8
/~LDAC+7: J44.3, J46.8
/~LDAC-0: J5.2, J7.7
/~LDAC-1: J14.2, J16.7
/~LDAC-2: J19.2, J21.7
/~LDAC-3: J34.2, J36.7
/~LDAC-4: J29.2, J31.7
/~LDAC-5: J24.2, J26.7
/~LDAC-6: J39.2, J41.7
/~LDAC-7: J44.2, J46.7
/~Shutdown_Reset: JA1.4, TP11.1, TP16.1, TP21.1, TP23.1, TP31.1, TP36.1, TP41.1, TP46.1, U13.6, U15.6, U16.6, U18.6, U20.6, U22.6, U24.6, U26.6
GND: C1.2, C2.2, C3.2, C4.2, C5.2, C6.2, C7.2, C8.2, C9.2, C10.2, C11.2, C12.2, C13.2, C14.2, C15.2, C16.1, C17.1, C18.1, C19.1, C20.2, C21.1, C22.2, C23.2, C24.2, C25.1, C26.1, C27.1, C28.1, C29.1, C30.1, C31.1, C32.1, C33.1, C34.1, C35.1, C36.1, C37.1, C38.2, C39.1, C40.2, C41.2, C42.1, C43.2, C44.2, C45.1, C46.2, C47.2, C48.1, C49.2, C50.2, C51.1, C52.2, C53.2, C54.1, C55.2, C56.2, C57.1, C58.2, C59.2, C60.1, C61.2, C62.2, C63.2, C64.2, C65.2, C66.2, D2.1, D3.1, D4.1, D5.1, D6.1, D7.1, D8.1, D9.1, D10.1, D11.1, D12.1, H4.1, H5.1, H7.1, H9.1, H11.1, H12.1, H13.1, H14.1, H15.1, J2.5, J2.6, J2.9, J2.10, J2.20, J2.26, J2.27, J2.28, J3.9, J3.10, J3.15, J3.16, J3.21, J3.22, J3.27, J3.28, J3.33, J3.34, J4.2, J4.SH, J5.1, J5.6, J5.11, J5.16, J5.19, J5.24, J5.25, J5.26, J5.30, J6.SH, J7.SH, J9.2, J9.5, J10.2, J10.5, J11.2, J11.5, J12.3, J12.5, J13.2, J13.SH, J14.1, J14.6, J14.11, J14.16, J14.19, J14.24, J14.25, J14.26, J14.30, J15.SH, J16.SH, J18.2, J18.SH, J19.1, J19.6, J19.11, J19.16, J19.19, J19.24, J19.25, J19.26, J19.30, J20.SH, J21.SH, J23.2, J23.SH, J24.1, J24.6, J24.11, J24.16, J24.19, J24.24, J24.25, J24.26, J24.30, J25.SH, J26.SH, J28.2, J28.SH, J29.1, J29.6, J29.11, J29.16, J29.19, J29.24, J29.25, J29.26, J29.30, J30.SH, J31.SH, J33.2, J33.SH, J34.1, J34.6, J34.11, J34.16, J34.19, J34.24, J34.25, J34.26, J34.30, J35.SH, J36.SH, J38.2, J38.SH, J39.1, J39.6, J39.11, J39.16, J39.19, J39.24, J39.25, J39.26, J39.30, J40.SH, J41.SH, J43.2, J43.SH, J44.1, J44.6, J44.11, J44.16, J44.19, J44.24, J44.25, J44.26, J44.30, J45.SH, J46.SH, J48.SH, JA1.9, JA1.10, JA1.15, JA1.16, JA1.21, JA1.22, JA1.27, JA1.28, JA1.33, JA1.34, JA2.9, JA2.10, JA2.15, JA2.16, JA2.21, JA2.22, JA2.27, JA2.28, JA2.33, JA2.34, JB1.9, JB1.10, JB1.15, JB1.16, JB1.21, JB1.22, JB1.27, JB1.28, JB1.33, JB1.34, JB2.9, JB2.10, JB2.15, JB2.16, JB2.21, JB2.22, JB2.27, JB2.28, JB2.33, JB2.34, JC1.9, JC1.10, JC1.15, JC1.16, JC1.21, JC1.22, JC1.27, JC1.28, JC1.33, JC1.34, JP2.2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
GNDPWR: H2.1, H3.1, H6.1, H8.1, H10.1, J8.1, J17.1, J22.1, J27.1, J32.1, J37.1, J42.1, J47.1, TP13.1, TP18.1, TP27.1, TP28.1, TP33.1, TP38.1, TP43.1, TP48.1
unnamed: C10.1, C18.2, J11.3, R10.2
unnamed: C2.1, C16.2, J9.3, R3.2
unnamed: C3.1, C17.2, J10.3, R4.2
unnamed: C19.2, C20.1, J12.1, R11.2
unnamed: C22.1, JP16.2, U4.20
unnamed: C23.1, JP24.2, U5.20
unnamed: C34.2, JP31.1, L1.2, U11.1
unnamed: C61.1, U27.67
unnamed: C62.1, J48.12
unnamed: C63.1, J48.6
unnamed: C64.1, J48.1
unnamed: C65.1, J48.7
unnamed: C66.1, R50.2
unnamed: D1.1, R6.2
unnamed: D1.2, J1.1
unnamed: D2.2, R8.2
unnamed: D3.2, R9.2
unnamed: D4.2, R17.1
unnamed: D5.2, R12.2
unnamed: D6.2, R22.1
unnamed: D7.2, R26.1
unnamed: D8.2, R30.1
unnamed: D9.2, R34.1
unnamed: D10.2, R38.1
unnamed: D11.2, R42.1
unnamed: D12.2, R46.1
unnamed: D13.2, R52.2
unnamed: F1.2, R5.1, R6.1
unnamed: J1.2, R7.2
unnamed: J48.2, U27.6
unnamed: J48.3, U27.7
unnamed: J48.4, U27.10
unnamed: J48.5, U27.9
unnamed: J48.8, U27.4
unnamed: J48.9, U27.3
unnamed: J48.10, U27.12
unnamed: J48.11, U27.13
unnamed: J48.13, R49.1
unnamed: J48.15, R47.1
unnamed: JA1.1, R13.1
unnamed: JP1.2, JP2.1, U2.31
unnamed: JP3.2, U2.2
unnamed: JP4.2, U2.8
unnamed: JP5.2, U2.32
unnamed: JP6.2, U2.19
unnamed: JP7.2, JP8.1, U3.31
unnamed: JP9.2, U3.2
unnamed: JP10.2, U3.8
unnamed: JP11.2, U3.32
unnamed: JP12.2, U3.19
unnamed: JP13.2, U4.1
unnamed: JP14.2, U4.2
unnamed: JP15.2, U4.3
unnamed: JP17.1, U4.4
unnamed: JP18.1, U4.7
unnamed: JP19.1, U4.11
unnamed: JP20.1, U4.14
unnamed: JP21.2, U5.1
unnamed: JP22.2, U5.2
unnamed: JP23.2, U5.3
unnamed: JP25.1, U5.4
unnamed: JP26.1, U5.7
unnamed: JP27.1, U5.11
unnamed: JP28.1, U5.14
unnamed: JP29.2, U6.7
unnamed: JP30.2, U10.3
unnamed: JP32.2, U27.61
unnamed: JP33.1, U27.62
unnamed: JP34.2, U27.56
unnamed: JP35.2, U27.48
unnamed: JP36.2, U27.57
unnamed: L1.1, R18.1
unnamed: Q1.1, R64.1
unnamed: Q2.1, R19.1
unnamed: Q3.1, R23.1
unnamed: Q4.1, R27.1
unnamed: Q5.1, R31.1
unnamed: Q6.1, R35.1
unnamed: Q7.1, R39.1
unnamed: Q8.1, R43.1
unnamed: R21.1, U12.2
unnamed: R25.1, U14.2
unnamed: R29.1, U17.2
unnamed: R33.1, U19.2
unnamed: R37.1, U21.2
unnamed: R41.1, U23.2
unnamed: R45.1, U25.2
unnamed: R48.1, U27.1
unnamed: R51.2, U27.50
unnamed: R66.1, U1.2
unnamed: RN3.3, U27.32
unnamed: RN3.4, U27.30
unnamed: RN3.5, U27.29
unnamed: RN3.6, U27.27
unnamed: RN3.7, U27.26
unnamed: RN3.8, U27.25
unnamed: TP50.1, U27.15
unnamed: TP51.1, U27.16
unnamed: TP52.1, U27.55
unnamed: TP53.1, U27.54
unnamed: U1.4, U16.1
unnamed: U12.4, U13.1
unnamed: U13.2, U13.3
unnamed: U14.4, U15.1
unnamed: U15.2, U15.3
unnamed: U16.2, U16.3
unnamed: U17.4, U18.1
unnamed: U18.2, U18.3
unnamed: U19.4, U20.1
unnamed: U20.2, U20.3
unnamed: U21.4, U22.1
unnamed: U22.2, U22.3
unnamed: U23.4, U24.1
unnamed: U24.2, U24.3
unnamed: U25.4, U26.1
unnamed: U26.2, U26.3
unnamed: U27.17, U27.34
VD: C4.1, C31.2, F1.1, R18.2, TP5.1
